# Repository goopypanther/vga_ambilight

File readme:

VGA adapter for homemade ambient lighting through RGB led strips.
Designed with this in mind: https://www.adafruit.com/products/285
Although other suppliers/strips are certainly compatible.
Note: analog strips only, not digital.

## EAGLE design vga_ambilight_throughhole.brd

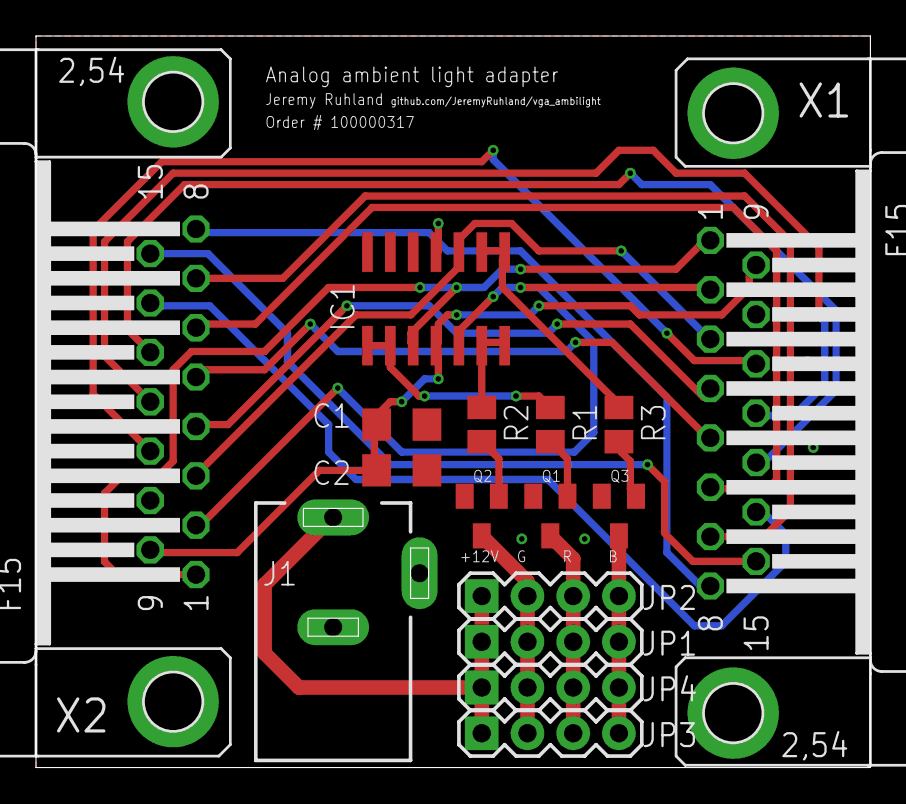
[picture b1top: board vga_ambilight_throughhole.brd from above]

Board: 2 copper layers, 46.4 x 40.6 mm, 16 parts (0 on the bottom side), 25 nets.

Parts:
C1: 10uf; C1206
C2: 0.1uf; C1206
IC1: QUAD_OPAMPD; SO14
J1: DCJ0303
JP1, JP2, JP3, JP4: 1X04
Q1, Q2, Q3: SOT23
R1, R2, R3: M0805
X1, X2: F15HP

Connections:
+12V: J1.1, JP1.1, JP2.1, JP3.1, JP4.1
B: IC1.10, X1.3, X2.3
B_PWR: JP1.4, JP2.4, JP3.4, JP4.4, Q3.3
G: IC1.5, X1.2, X2.2
GND: C1.2, C2.2, IC1.11, J1.2, J1.3, Q1.2, Q2.2, Q3.2, X1.10, X2.10
G_PWR: JP1.2, JP2.2, JP3.2, JP4.2, Q2.3
unnamed: X1.4, X2.4
unnamed: X1.5, X2.5
unnamed: X1.6, X2.6
unnamed: X1.7, X2.7
unnamed: X1.8, X2.8
unnamed: IC1.8, IC1.9, R3.1
unnamed: IC1.6, IC1.7, R2.1
unnamed: IC1.1, IC1.2, R1.1
unnamed: X1.15, X2.15
unnamed: X1.14, X2.14
unnamed: X1.13, X2.13
unnamed: Q1.1, R1.2
unnamed: Q2.1, R2.2
unnamed: X1.11, X2.11
unnamed: X1.12, X2.12
unnamed: Q3.1, R3.2
R: IC1.3, X1.1, X2.1
R_PWR: JP1.3, JP2.3, JP3.3, JP4.3, Q1.3
VCC: C1.1, C2.1, IC1.4, X1.9, X2.9

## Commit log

2012-07-08 fist commit
2012-07-11 added image
2012-07-11 led strip info in readme

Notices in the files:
parts and their libraries:
sparkfun: Licensing: CC v3.0 Share-Alike You are welcome to use this library for commercial purposes.
